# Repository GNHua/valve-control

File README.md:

# valve-control

Use Arduino Uno to control solenoid valves.  
Follow the steps below to set up your own valve control station.

## Purchase

### Solenoid Valves

* [Clippard, E310C-2C012, 10 mm N-C 3-way Valve, In-line Connector w/LED, 0.030" Orifice, 1.3W, 12 VDC](http://www.clippard.com/part/E310C-2C012)
* [Valve connector cable](http://www.clippard.com/products/electronic-valve-10mm-connector)
* [Manifold](http://www.clippard.com/products/electronic-valve-10mm-manifolds)

Details can be found on page 215-221 in [Clippard Full-line Catalog](http://www.clippard.com/downloads/PDF_Documents/Clippard%20Full%20Line%20Catalog/Clippard%20Full-Line%20Catalog.pdf)

### Send [PCB design](https://github.com/GNHua/valve-control/raw/master/pcb_layout/plots.zip) Out For Manufacturing

* Highly recommend [JLCPCB](https://jlcpcb.com/). Fabrication and shipping took ~1 week for me in the U.S.
* If you choose JLCPCB, go [here](https://jlcpcb.com/quote), upload [plots.zip](pcb_layout/plots.zip), and leave everything else as default.
* If you have access to a PCB baking oven, buying a SMT-Stencil will save you a lot of time for soldering. If not, all the components can still be soldered by hand.

| Top Layer | Bottom Layer |
| --------- | ------------ |
|  |  |

### Electrical Components To Buy

| Part | Label on PCB | Qty. (per PCB) | Purchase |
| ---- | :----------- | :------------: | :------: |
| [Shift register, SN74HC595N](https://www.digikey.com/product-detail/en/texas-instruments/SN74HC595N/296-1600-5-ND/277246?utm_adgroup=Integrated%20Circuits&slid=&gclid=Cj0KCQjwzK_bBRDDARIsAFQF7zN5-LHxIfRLcNVY-gf6gJ_lS_RSs-WGzMVOjYGovQlShfyqFOsZDr0aAqcmEALw_wcB) | plug on the DIP socket (U1) | 1 | [link](https://www.digikey.com/product-detail/en/texas-instruments/SN74HC595N/296-1600-5-ND/277246?utm_adgroup=Integrated%20Circuits&slid=&gclid=Cj0KCQjwzK_bBRDDARIsAFQF7zN5-LHxIfRLcNVY-gf6gJ_lS_RSs-WGzMVOjYGovQlShfyqFOsZDr0aAqcmEALw_wcB)
| [Optoisolator, HCPL 2731](https://www.digikey.com/product-detail/en/on-semiconductor/HCPL2731/HCPL2731QT-ND/31642) | plug on the DIP sockets (U2-U5) | 4 | [link](https://www.digikey.com/product-detail/en/on-semiconductor/HCPL2731/HCPL2731QT-ND/31642) |
| [Resistor, 2.32 k&Omega;, package 0805](https://www.digikey.com/product-detail/en/stackpole-electronics-inc/RMCF0805FT2K32/RMCF0805FT2K32DKR-ND/1943295) | R1-R16 | 16 | [link](https://www.digikey.com/product-detail/en/stackpole-electronics-inc/RMCF0805FT2K32/RMCF0805FT2K32DKR-ND/1943295) |
| [Common anode diode](https://www.digikey.com/product-detail/en/diodes-incorporated/BAT54AT-7-F/BAT54AT-FDICT-ND/821941) | D1-D4 | 4 | [link](https://www.digikey.com/product-detail/en/diodes-incorporated/BAT54AT-7-F/BAT54AT-FDICT-ND/821941) |
| [PMOS](https://www.digikey.com/product-detail/en/toshiba-semiconductor-and-storage/SSM3J338RLF/SSM3J338RLFCT-ND/5810258) | Q1-Q8 | 8 | [link](https://www.digikey.com/product-detail/en/toshiba-semiconductor-and-storage/SSM3J338RLF/SSM3J338RLFCT-ND/5810258) |
| [1 uF capacitor, package 0805, voltage rating 10V](https://www.digikey.com/product-detail/en/yageo/CC0805KKX7R6BB105/311-1458-1-ND/2833764) | C1 | 1 | [link](https://www.digikey.com/product-detail/en/yageo/CC0805KKX7R6BB105/311-1458-1-ND/2833764) |
| [DIP socket, 2x8](https://www.digikey.com/product-detail/en/assmann-wsw-components/A-16-LC-TT/AE9992-ND/821746) | U1 | 1 | [link](https://www.digikey.com/product-detail/en/assmann-wsw-components/A-16-LC-TT/AE9992-ND/821746) |
| [DIP socket, 2x4](https://www.digikey.com/product-detail/en/assmann-wsw-components/A-08-LC-TT/AE9986-ND/821740) | U2-U5 | 4 | [link](https://www.digikey.com/product-detail/en/assmann-wsw-components/A-08-LC-TT/AE9986-ND/821740) |
| [Stacking headers](https://www.digikey.com/products/en?mpart=85&v=1528) | J2-J4, H1, H2 | 1 | [link](https://www.digikey.com/products/en?mpart=85&v=1528) |
| [Connector, Molex 50212-8000](https://www.digikey.com/product-detail/en/molex-llc/50212-8000/WM4561CT-ND/2524899) | N/A | 18 | [link](https://www.digikey.com/product-detail/en/molex-llc/50212-8000/WM4561CT-ND/2524899) |
| [Connector housing, Molex 0873690200](https://www.digikey.com/product-detail/en/molex-llc/0873690200/WM10118-ND/3264531) | N/A | 9 | [link](https://www.digikey.com/product-detail/en/molex-llc/0873690200/WM10118-ND/3264531) |
| [JST header, Molex 0894010210](https://www.digikey.com/products/en?keywords=0894010210) | J5-J13 | 9 | [link](https://www.digikey.com/products/en?keywords=0894010210) |
| [2.5 mm barrel jack, 5A max, CUI PJ-057BH ](https://www.digikey.com/product-detail/en/cui-inc/PJ-057BH/CP-057BH-ND/1644602?WT.srch=1&gclid=Cj0KCQjwzK_bBRDDARIsAFQF7zMAA_lLykibpOltGBij_q3GgaALm4U1mWajtnpzEGkrmGGN8nhqwBUaAmMTEALw_wcB) | J1 | 1 for each setup | [link](https://www.digikey.com/product-detail/en/cui-inc/PJ-057BH/CP-057BH-ND/1644602?WT.srch=1&gclid=Cj0KCQjwzK_bBRDDARIsAFQF7zMAA_lLykibpOltGBij_q3GgaALm4U1mWajtnpzEGkrmGGN8nhqwBUaAmMTEALw_wcB) |

## Download

Download [zip](https://github.com/GNHua/valve-control/archive/master.zip) and extract all files.

## Prepare Software

### Flash Arduino Uno

* Connect an Arduino Uno to computer via USB
* Download and Install [Arduino IDE](https://www.arduino.cc/en/Main/Software)
* Open `arduino_valve_control.ino` in `arduino_valve_control` folder with Arduino IDE
* Select USB port: `Tools` > `Port`
* Click `Upload` (the right arrow at the top left corner)
* Wait for uploading to complete

### Python

* Download and Install Python 3.6
  * The Python distribution, [Anaconda](https://www.anaconda.com/download) is recommended, because it comes with pre-installed packages. 
  * Note: On Windows, the directory of installed Python must be added to environment variable. 
* Install Python dependencies
  * Windows: double click `platforms/windows/setup.bat`
  * MacOSX: `$ bash <path to>/platforms/macosx/setup.sh`

## Soldering

(ADD photos of top and bottom layer after soldering)

Solder all the components according to the [table above](#Electrical-Components-To-Buy). The surface mount components are soldered to the bottom layer, while the rest are mounted on the top layer.

### Stacking Headers

In the [table above](#Electrical-Components-To-Buy), the [stacking headers](https://www.digikey.com/products/en?mpart=85&v=1528) contains the following headers.

| Stacking Header | Label on PCB         | Qty. |
| --------------- | :------------------- | :--: |
| 1 x 10          | cut out a 1x2 for J4 | 1    |
| 1 x  8          | H1, H2               | 2    |
| 1 x  6          |                      | 2    |
| 2 x  3          | J2+J3                | 1    |

### H3 - 5V and GND

Because the JST headers at J11 and J12 block H3 on the top layer, I would do the following:

1. Cut a 1x2 stacking header out of an unused one
2. Solder it on H3 from the bottom layer
3. Cut off the female portion on the top layer
4. Put more solder from the top layer

### Barrel Jack

Each setup only needs one barrel jack to connect to a 12 V power supply. The barrel jack can be soldered on any one of the boards.

## Assembly

### Shift Register and Optoisolators

(The images shown below are all taken for the previous PCB design, which is marginally different from the current design.)

After soldering, plug the shift register and optoisolators into their corresponding DIP sockets. Refer to the following image for their orientation.

### Stacking PCBs

#### For the inpatient

1. Bend or remove the data pins on all boards except Board 1. See the left image below.
2. Make a connector for serial input and serial output. See the right image below.
3. Stack the PCBs and plug in the connector just made.

| Data Pin | Serial Input/Output |
| -------- | ------------------- |
|  |  |

#### Details

In the images above, there are 4 boards stacked on an Arduino Uno.  
Each board provides 8 solenoid valve connectors, and the current design supports up to 6 boards.  
**Before putting the boards together, the data pins on all boards except Board 1 must be bent or removed.**
This is because the data pin connects to the serial input of shift register.
On Board 1, the shift register receives data from the Arduino directly.
For the Board 2-n, their shift registers must have its serial input connected to the serial output of board right beneath it.

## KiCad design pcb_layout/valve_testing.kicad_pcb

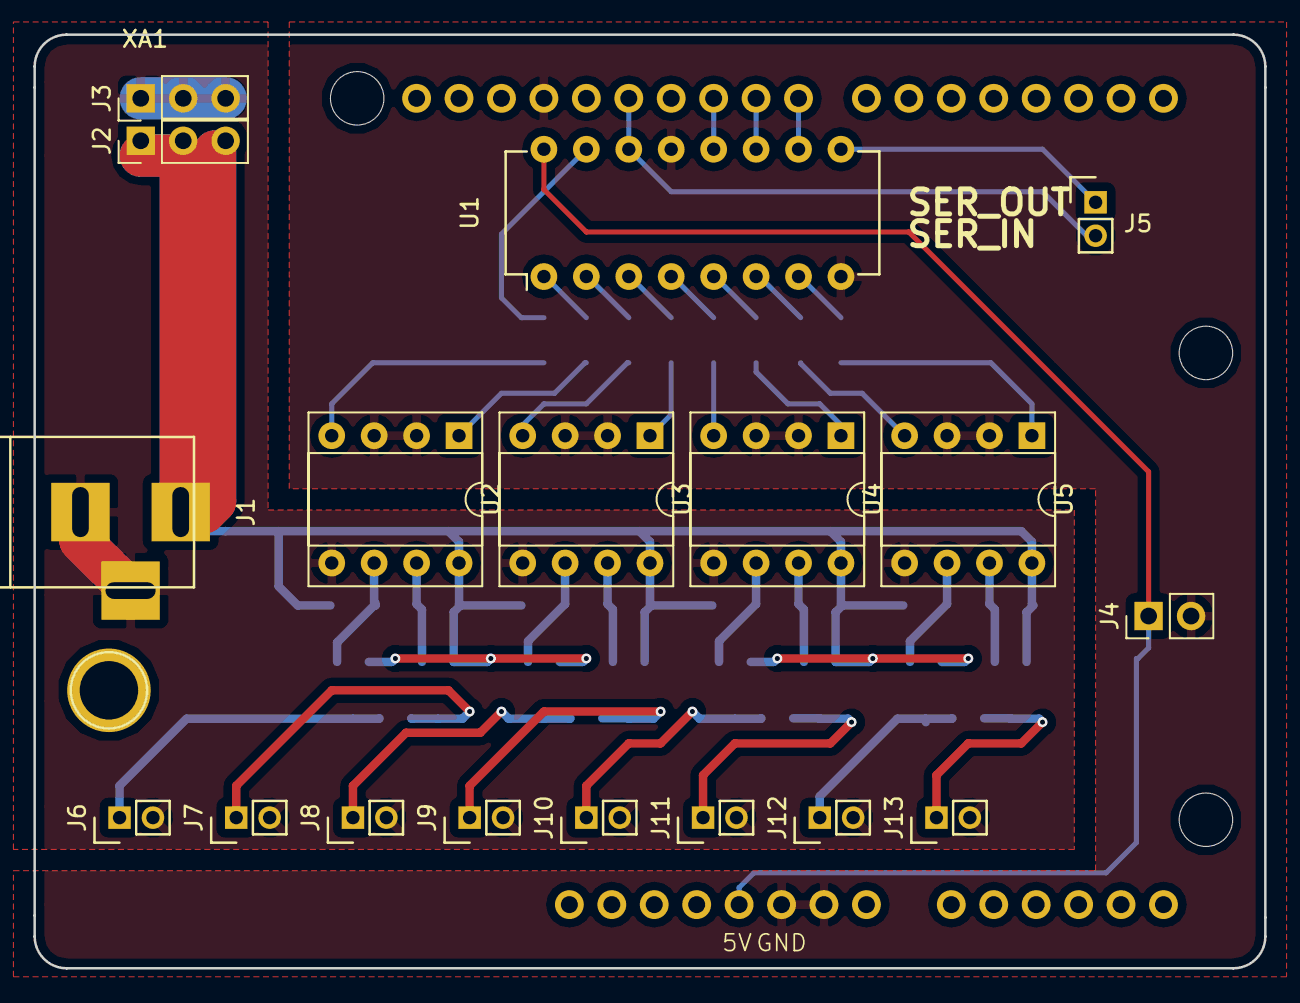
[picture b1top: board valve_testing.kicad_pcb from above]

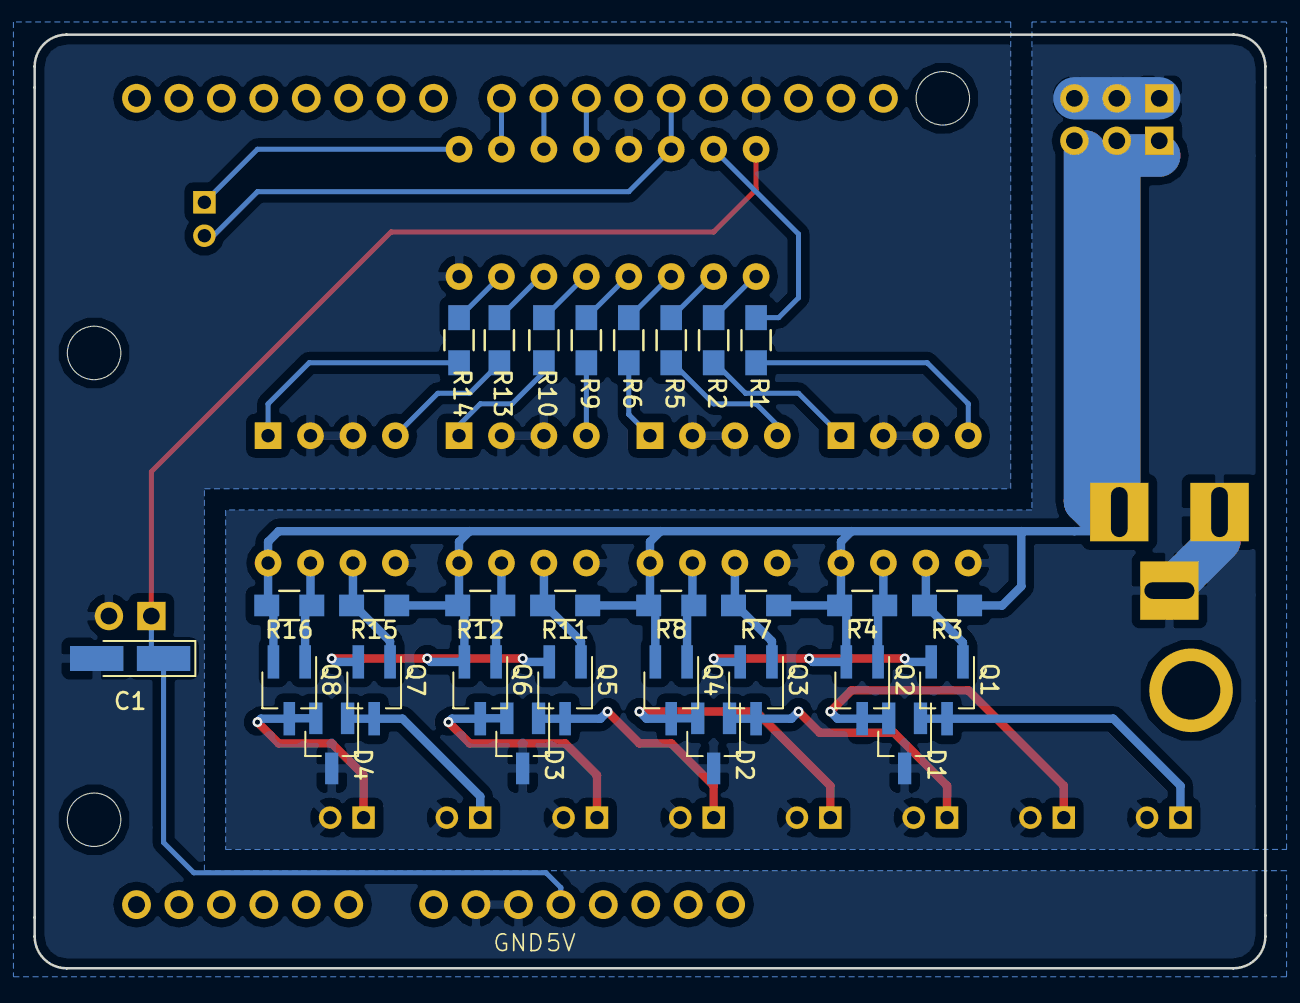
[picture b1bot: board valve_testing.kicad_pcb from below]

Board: 2 copper layers, 73.7 x 55.9 mm, 48 parts (29 on the bottom side), 40 nets.

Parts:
C1: 1u; CP_Tantalum_Case-A_EIA-3216-18_Hand
D1, D2, D3, D4: D_Schottky_x2_ACom_KKA; SOT-23_Handsoldering
J1: Barrel_Jack; BARREL_JACK
J2, J3: Conn_01x04; Pin_Header_Straight_1x03_Pitch2.54mm
J4: Conn_01x02; Pin_Header_Straight_1x02_Pitch2.54mm
J5, J6, J7, J8, J9, J10, J11, J12, J13: Conn_01x02; Pin_Header_Straight_1x02_Pitch2.00mm
Q1, Q2, Q3, Q4, Q5, Q6, Q7, Q8: Q_PMOS_GSD; SOT-23W_Handsoldering
R1, R2, R3, R4, R5, R6, R7, R8, R9, R10, R11, R12, R13, R14, R15, R16: 2.32k; R_0805_HandSoldering
U1: 74HC595; DIP-16_W7.62mm
U2, U3, U4, U5: HCPL2731; DIP-8_W7.62mm_Socket
XA1: Arduino_Uno_Shield

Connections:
/QA: R1.1, U1.15
/QB: R2.1, U1.1
/QC: R5.1, U1.2
/QD: R6.1, U1.3
/QE: R9.1, U1.4
/QF: R10.1, U1.5
/QG: R13.1, U1.6
/QH: R14.1, U1.7
/SRCLR: U1.10, XA1.D8
/clockPin: U1.11, XA1.D9
/dataPin: J5.2, U1.14, XA1.D12
/latchPin: U1.12, XA1.D10
GND: C1.2, D1.3, D2.3, D3.3, D4.3, J1.2, J1.3, J3.1, J3.2, J3.3, J4.2, J6.2, J7.2, J8.2, J9.2, J10.2, J11.2, J12.2, J13.2, U1.8, U1.13, U2.2, U2.3, U2.5, U3.2, U3.3, U3.5, U4.2, U4.3, U4.5, U5.2, U5.3, U5.5, XA1.GND1, XA1.GND2, XA1.GND3
unnamed: D1.1, J6.1, Q1.3
unnamed: D1.2, J7.1, Q2.3
unnamed: D2.1, J8.1, Q3.3
unnamed: D2.2, J9.1, Q4.3
unnamed: D3.1, J10.1, Q5.3
unnamed: D3.2, J11.1, Q6.3
unnamed: D4.1, J12.1, Q7.3
unnamed: D4.2, J13.1, Q8.3
unnamed: J5.1, U1.9
unnamed: Q1.1, R3.2, U2.6
unnamed: Q2.1, R4.2, U2.7
unnamed: Q3.1, R7.2, U3.6
unnamed: Q4.1, R8.2, U3.7
unnamed: Q5.1, R11.2, U4.6
unnamed: Q6.1, R12.2, U4.7
unnamed: Q7.1, R15.2, U5.6
unnamed: Q8.1, R16.2, U5.7
unnamed: R1.2, U2.4
unnamed: R2.2, U2.1
unnamed: R5.2, U3.4
unnamed: R6.2, U3.1
unnamed: R9.2, U4.4
unnamed: R10.2, U4.1
unnamed: R13.2, U5.4
unnamed: R14.2, U5.1
VCC: C1.1, J4.1, U1.16, XA1.5V1
Vcc_12V: J1.1, J2.1, J2.2, J2.3, Q1.2, Q2.2, Q3.2, Q4.2, Q5.2, Q6.2, Q7.2, Q8.2, R3.1, R4.1, R7.1, R8.1, R11.1, R12.1, R15.1, R16.1, U2.8, U3.8, U4.8, U5.8

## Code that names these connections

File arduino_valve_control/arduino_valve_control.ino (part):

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#include "defaults.h"

#define MYPORT PORTB
#define SRCLR 8
#define dataPin 12
#define clockPin 9
#define latchPin 10
#define SRCLRBitLoc (SRCLR-8)
#define dataPinBitLoc (dataPin-8)
#define clockPinBitLoc (clockPin-8)
#define latchPinBitLoc (latchPin-8)

uint8_t regNum;    // number of registers used
char* currentState;        // keep track of shift register outputs
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    EEPROM.update(AFTER_PHASE_NUM_ADDR, (byte)(AFTER_PHASE_NUM));
  }
  
  pinMode(SRCLR, OUTPUT);
  MYPORT |= (1 << SRCLRBitLoc);
  
  pinMode(dataPin,  OUTPUT);
  pinMode(clockPin, OUTPUT);
  pinMode(latchPin, OUTPUT);
  
  // initialize timer1 
  noInterrupts();     // disable all interrupts
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
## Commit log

2018-08-01 init commit
2018-08-01 add version number
2018-08-01 add ducumentation action and update action
2018-08-01 add update function
2018-08-01 change __version__ to string
2018-08-01 sync valve state when stopped actuating
2018-08-01 fix a small bug
2018-08-01 get response from serial port on demand, uncheck all vavle after clear
2018-08-10 new pcb
2018-08-10 resize pcb image
2018-09-02 fix a typo
2018-09-30 Add more details on how to solder and assemble
2018-10-01 add an additional link for purchasing
